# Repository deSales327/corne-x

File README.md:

# corne-x

PCB reversível e sem fios no formato **Corne** (3×6 + 3 polegares por metade, 42 teclas),
com os mesmos componentes do [dust](https://github.com/hazels-garage/dust): switches Kailh X
(PG1425), díodos 1N4148 SOD-123, Seeed XIAO nRF52840 (BLE), interruptor de energia e
bateria LiPo com conector JST-XH.

| Frente | Verso |
| :---: | :---: |
|  |  |

## Estado
- Roteada nas duas camadas, com plano de GND.
- **DRC do KiCad 10: 0 violações e 0 ligações em falta** (ver as exceções abaixo).
- Gerbers e furação prontos em [`corne-x-gerbers.zip`](corne-x-gerbers.zip).

## Ficheiros
| Ficheiro | O que é |
|---|---|
| `corne-x.kicad_pcb` / `.kicad_pro` / `.kicad_dru` | Projeto KiCad 10 (placa, regras e exceções do DRC) |
| `corne-x-gerbers.zip` | Gerbers + furação (Excellon) para encomendar |
| `gerar_pcb.py` | 1.ª fase: layout, matriz e contorno (`python gerar_pcb.py <dust.kicad_pcb>`, precisa de `shapely`) |
| `finalizar_pcb.py` | 2.ª fase, com o Python do KiCad: JST-XH, furo, Freerouting, GND, DRC e gerbers |
| `mockup.py` / `mockup.svg` / `mockup.png` | Render ilustrativo das duas metades montadas |
| `preview.svg` | Vista técnica da matriz (colunas e linhas) |

Para regenerar tudo:

```
python gerar_pcb.py caminho/para/dust/pcbs/dust.kicad_pcb
"%LOCALAPPDATA%\Programs\KiCad\10.0\bin\python.exe" finalizar_pcb.py caminho/para/freerouting-2.5.0.jar
python mockup.py
```

O Freerouting 2.5 precisa do Java 25 ou mais recente.

## Bateria
- **J1**: JST-XH 2,50 mm vertical, de furos passantes, que serve nas duas faces. O pino 1 é o BAT+ e o pino 2 o BAT−.
- **H1**: furo de 3,2 mm ao lado do conector, para passar os fios da bateria, que fica por baixo da placa.
- **PWR1**: interruptor no BAT− (entre o BAT− e o GND), tal como no dust.
- O BAT+ vai para o pad de bateria do XIAO pelos furos do footprint.
- Atenção à altura: o JST-XH vertical tem cerca de 7 mm, bem mais do que os switches Kailh X.

## Matriz e pinos do XIAO
| Pino | Função | Pino | Função |
|---|---|---|---|
| D0 | c5 (indicador interno) | D7 | r0 (polegares) |
| D1 | c4 (indicador) | D8 | r1 (fila de baixo) |
| D2 | c3 (médio) | D9 | r2 (fila home) |
| D3 | c2 (anelar) | D10 | r3 (fila de cima) |
| D4 | c1 (mindinho) | D6 | livre |
| D5 | c0 (mindinho externo) | | |

- Os díodos têm o cátodo (pad 1) na linha, por isso o sentido é COL2ROW (no ZMK, `diode-direction = "col2row"`).
- Os polegares usam as colunas c3, c4 e c5 da linha r0.
- A metade direita é a mesma PCB virada: basta encomendar um único desenho.

## Exceções do DRC
Os footprints do Kailh X, do díodo e do XIAO vêm do dust, que foi fabricado e montado com eles. A geometria interna destes footprints não cumpre algumas regras genéricas, por isso há três exceções:

- **`corne-x.kicad_dru`**: permite 0,1 mm entre furos e pads *dentro* do mesmo footprint de switch ou díodo. Pistas e zonas continuam sujeitas às regras normais.
- **`pth_inside_courtyard`** (ignorada): o díodo passante fica de propósito entre os pinos do switch.
- **`lib_footprint_issues`** (ignorada): a biblioteca de footprints do autor não está instalada.

Regras de roteamento usadas: 0,2 mm de distância, pistas de 0,25 mm (algumas estreitam para 0,187 mm junto aos pads), vias de 0,6/0,3 mm e 0,2 mm até à borda. Tudo isto está dentro das capacidades normais da JLCPCB.

## Créditos
- Footprints e eletrónica: dust, de Jason Hazel (CC BY 4.0).
- Layout: Corne (crkbd), de foostan (MIT).
- Este projeto: CC BY 4.0.

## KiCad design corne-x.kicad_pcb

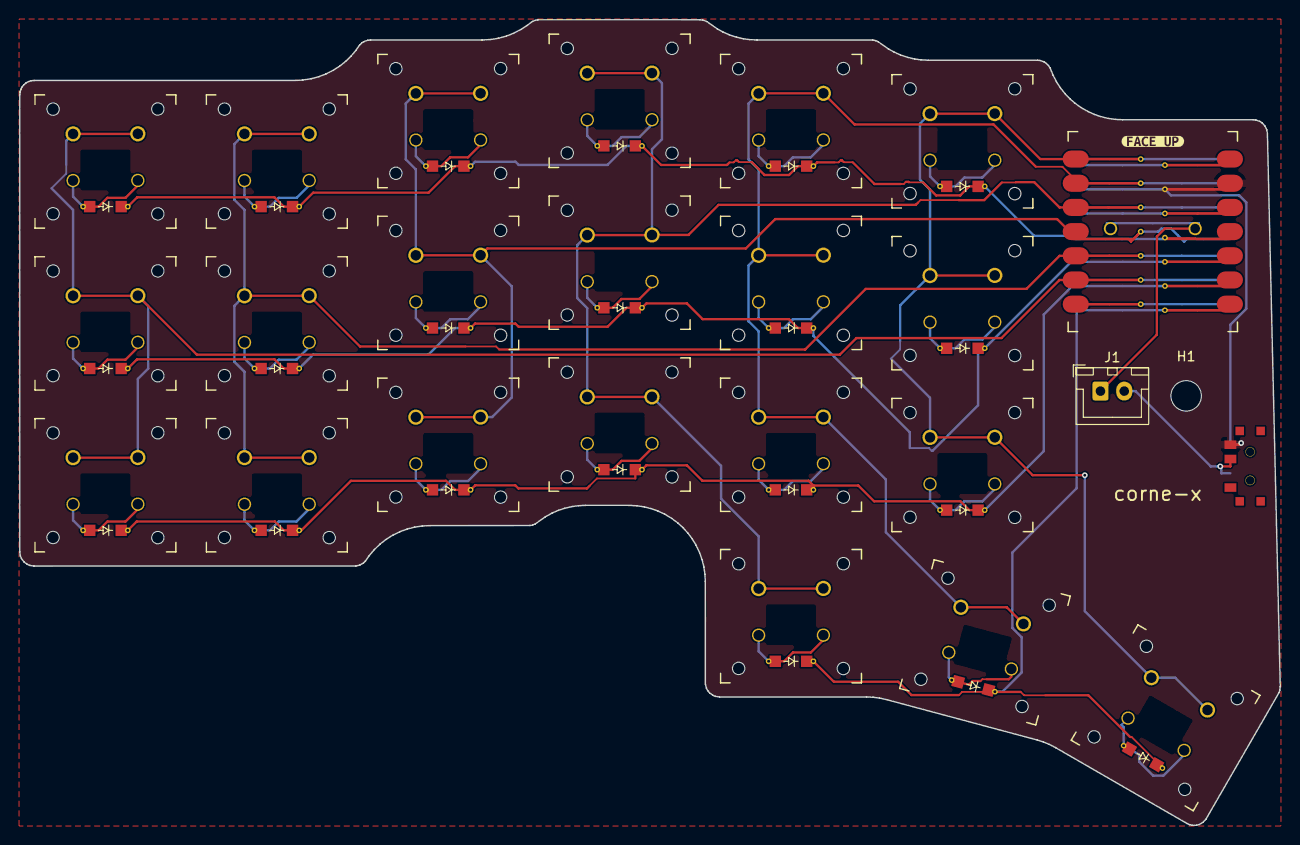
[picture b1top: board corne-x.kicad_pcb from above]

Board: 2 copper layers, 132.4 x 84.6 mm, 47 parts (1 on the bottom side), 34 nets.

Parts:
D1, D2, D3, D4, D5, D6, D7, D8, D9, D10, D11, D12, D13, D14, D15, D16, D17, D18, D19, D20, D21: ComboDiode
H1: MountingHole_3.2mm_M3
J1: JST_XH_B2B-XH-A_1x02_P2.50mm_Vertical
PWR1, PWR1#2: SPDT_C128955
S1, S2, S3, S4, S5, S6, S7, S8, S9, S10, S11, S12, S13, S14, S15, S16, S17, S18, S19, S20, S21: Kailh-PG1425-X-Switch-revers
XIAO1: xiao-rev

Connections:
BAT: J1.1, XIAO1.19
BAT-: J1.2, PWR1.2, PWR1#2.2
GND: PWR1.3, PWR1#2.1, XIAO1.13
c0: S1.1, S2.1, S3.1, XIAO1.6
c1: S4.1, S5.1, S6.1, XIAO1.5
c2: S7.1, S8.1, S9.1, XIAO1.4
c3: S10.1, S11.1, S12.1, S19.1, XIAO1.3
c4: S13.1, S14.1, S15.1, S20.1, XIAO1.2
c5: S16.1, S17.1, S18.1, S21.1, XIAO1.1
k_c0_r1: D3.2, S3.2
k_c0_r2: D2.2, S2.2
k_c0_r3: D1.2, S1.2
k_c1_r1: D6.2, S6.2
k_c1_r2: D5.2, S5.2
k_c1_r3: D4.2, S4.2
k_c2_r1: D9.2, S9.2
k_c2_r2: D8.2, S8.2
k_c2_r3: D7.2, S7.2
k_c3_r0: D19.2, S19.2
k_c3_r1: D12.2, S12.2
k_c3_r2: D11.2, S11.2
k_c3_r3: D10.2, S10.2
k_c4_r0: D20.2, S20.2
k_c4_r1: D15.2, S15.2
k_c4_r2: D14.2, S14.2
k_c4_r3: D13.2, S13.2
k_c5_r0: D21.2, S21.2
k_c5_r1: D18.2, S18.2
k_c5_r2: D17.2, S17.2
k_c5_r3: D16.2, S16.2
r0: D19.1, D20.1, D21.1, XIAO1.8
r1: D3.1, D6.1, D9.1, D12.1, D15.1, D18.1, XIAO1.9
r2: D2.1, D5.1, D8.1, D11.1, D14.1, D17.1, XIAO1.10
r3: D1.1, D4.1, D7.1, D10.1, D13.1, D16.1, XIAO1.11
